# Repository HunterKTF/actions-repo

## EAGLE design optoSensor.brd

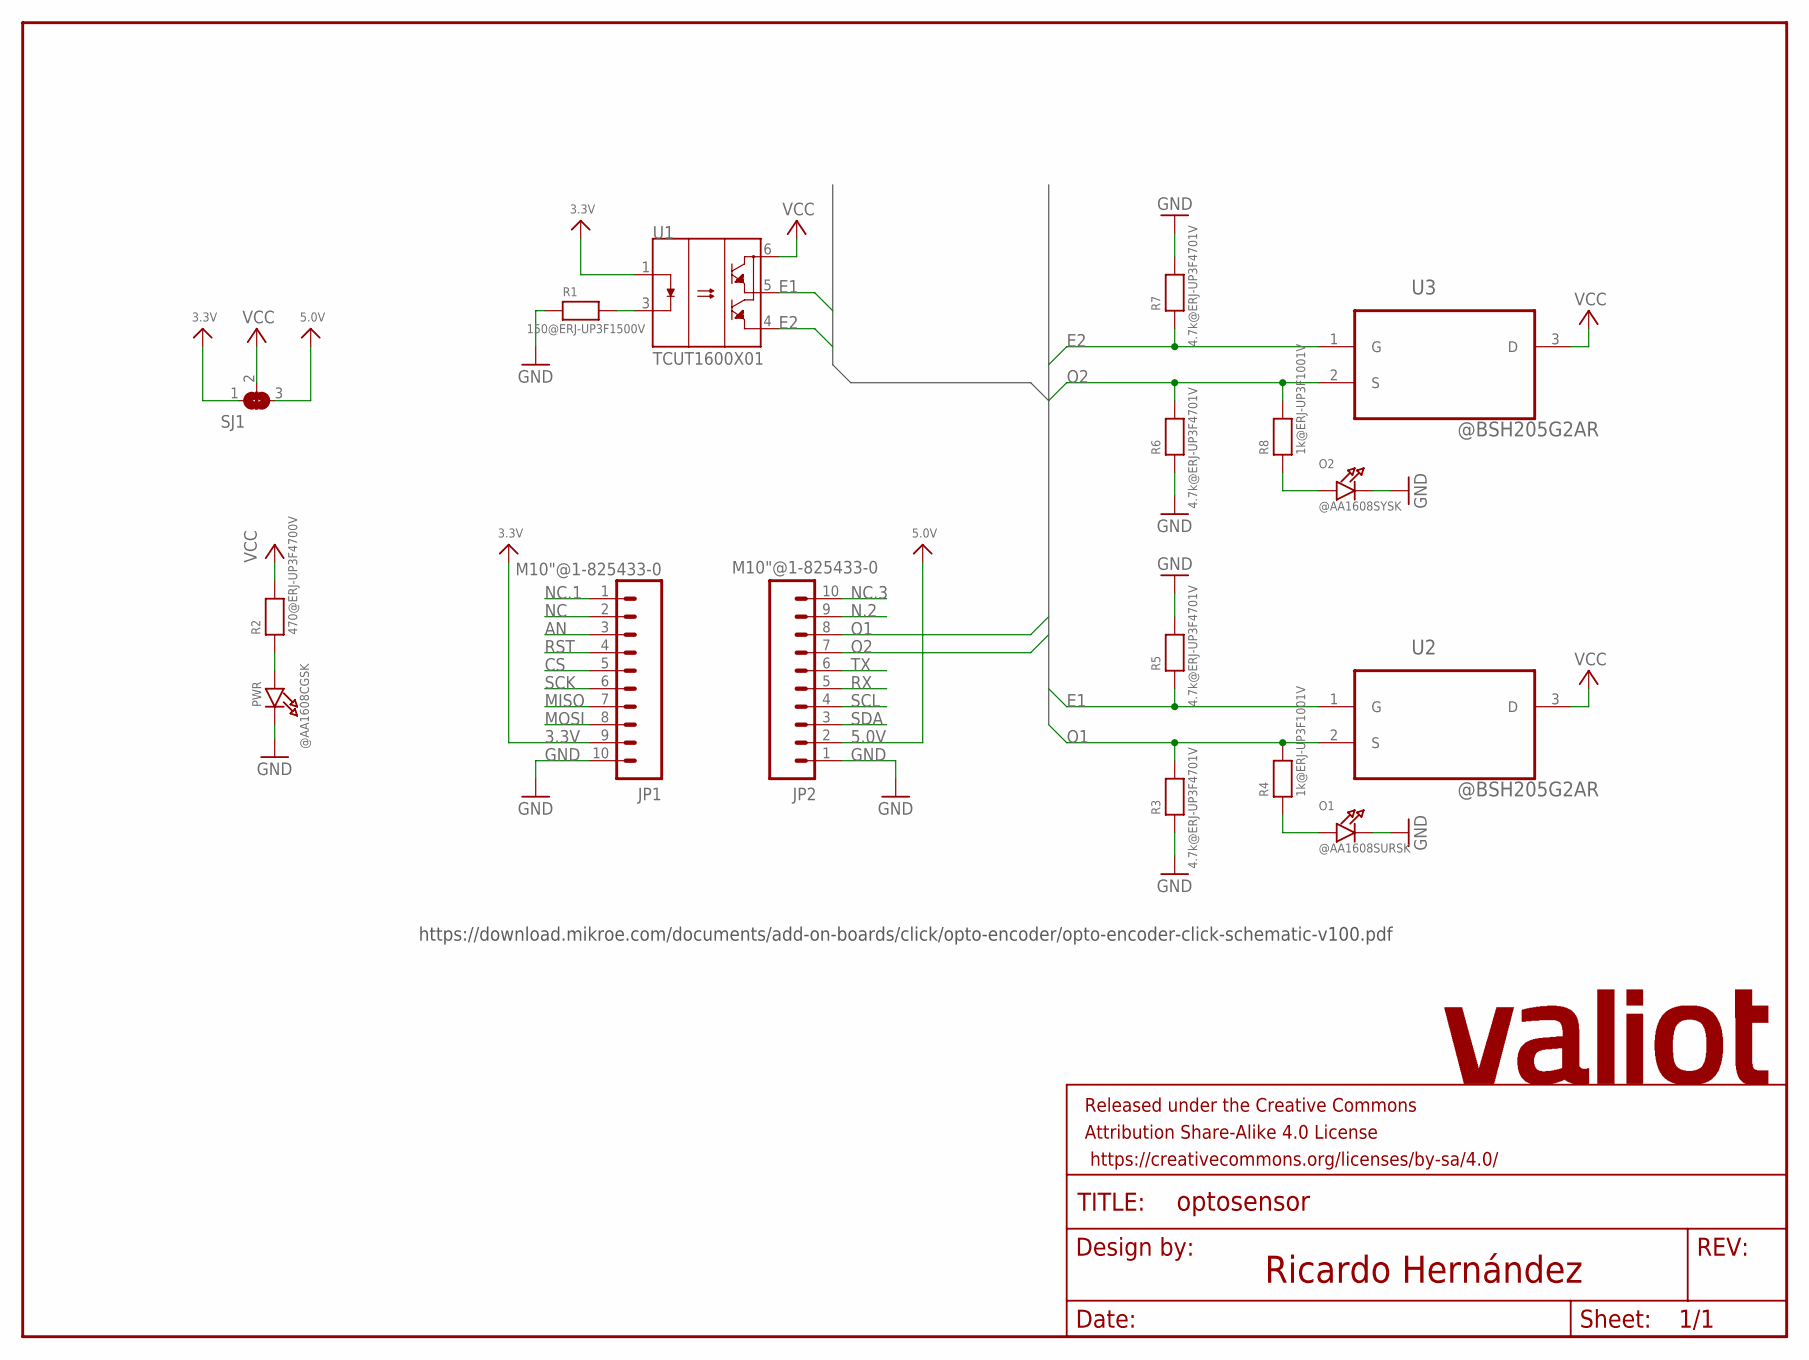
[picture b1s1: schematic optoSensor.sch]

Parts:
FRAME1: FRAME-LETTER; CREATIVE_COMMONS
JP1, JP2: M10"@1-825433-0; 1X10
O1: @AA1608SURSK; CHIPLED_0603_NOOUTLINE
O2: @AA1608SYSK; CHIPLED_0603_NOOUTLINE
PWR: @AA1608CGSK; CHIPLED_0603_NOOUTLINE
R1: 150@ERJ-UP3F1500V; 0603
R2: 470@ERJ-UP3F4700V; 0603
R3, R5, R6, R7: 4.7k@ERJ-UP3F4701V; 0603
R4, R8: 1k@ERJ-UP3F1001V; 0603
SJ1: SOLDERJUMPER_2WAY0603; SOLDERJUMPER_2WAY_OPEN_0603
U1: TCUT1600X01; XDCR_TCUT1600X01
U2, U3: @BSH205G2AR; SOT103P240X110-3N

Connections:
3.3V: JP1.9, SJ1.1, U1.1 (A)
5.0V: JP2.2, SJ1.3
AN: JP1.3
CS: JP1.5
E1: R5.1, U1.5 (E1), U2.1 (G)
E2: R7.1, U1.4 (E2), U3.1 (G)
GND: JP1.10, JP2.1, O1.C, O2.C, PWR.C, R1.1, R3.1, R5.2, R6.1, R7.2
MISO: JP1.7
MOSI: JP1.8
unnamed: R1.2, U1.3 (CATH)
unnamed: PWR.A, R2.1
unnamed: O1.A, R4.1
unnamed: O2.A, R8.1
N.2: JP2.9
NC: JP1.2
NC.1: JP1.1
NC.3: JP2.10
O1: JP2.8, R3.2, R4.2, U2.2 (S)
O2: JP2.7, R6.2, R8.2, U3.2 (S)
RST: JP1.4
RX: JP2.5
SCK: JP1.6
SCL: JP2.4
SDA: JP2.3
TX: JP2.6
VCC: R2.2, SJ1.2, U1.6 (COLL), U2.3 (D), U3.3 (D)

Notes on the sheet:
https://download.mikroe.com/documents/add-on-boards/click/opto-encoder/opto-encoder-click-schematic-v100.pdf
Ricardo Hernández

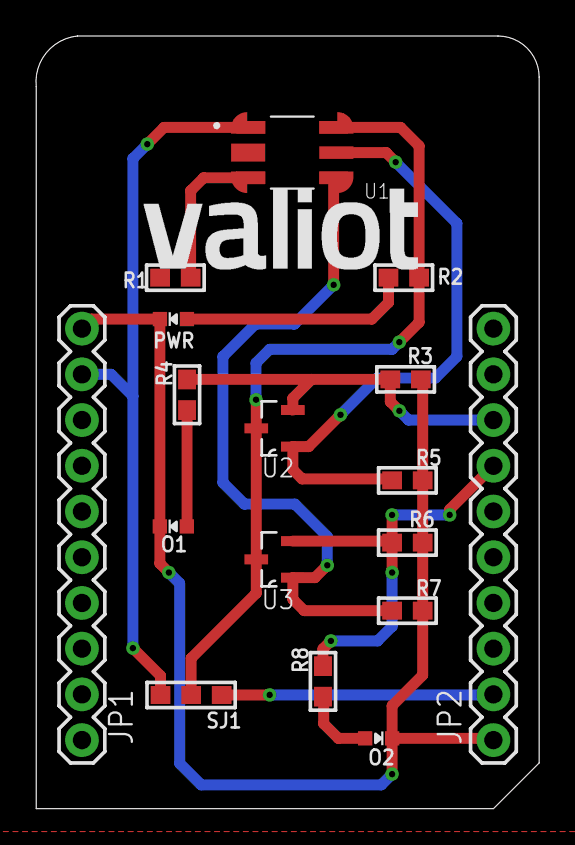
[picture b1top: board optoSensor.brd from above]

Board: 2 copper layers, 28.0 x 42.9 mm, 19 parts (0 on the bottom side), 12 nets.

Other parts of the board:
U$7: VALIOT_15X5MM

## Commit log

2021-06-10 github action
2021-06-10 added python
2021-06-11 using docker in vm
2021-06-11 updated docker action
2021-06-11 changes to docker action
2021-06-11 sudo docker file run
2021-06-11 test
2021-06-12 added sh for testing
2021-06-12 added requirements for python
2021-06-13 added start.sh
2021-06-13 Added full Eagle workflow
2021-06-13 Minor bug
2021-06-13 check eagle
2021-06-14 added files
2021-06-14 new creds file for python app
2021-06-14 Rename creds.js to creds.json
2021-06-15 Added a Coma
2021-06-15 added libraries

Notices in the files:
parts and their libraries:
SparkFun-Aesthetics: Licensing: Creative Commons ShareAlike 4.0 International - https://creativecommons.org/licenses/by-sa/4.0
SparkFun-Aesthetics: Released under the Creative Commons Attribution Share-Alike 4.0 License
SparkFun-Aesthetics: https://creativecommons.org/licenses/by-sa/4.0
